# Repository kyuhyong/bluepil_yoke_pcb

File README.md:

# bluepil_yoke_pcb
# bluepil_yoke_pcb

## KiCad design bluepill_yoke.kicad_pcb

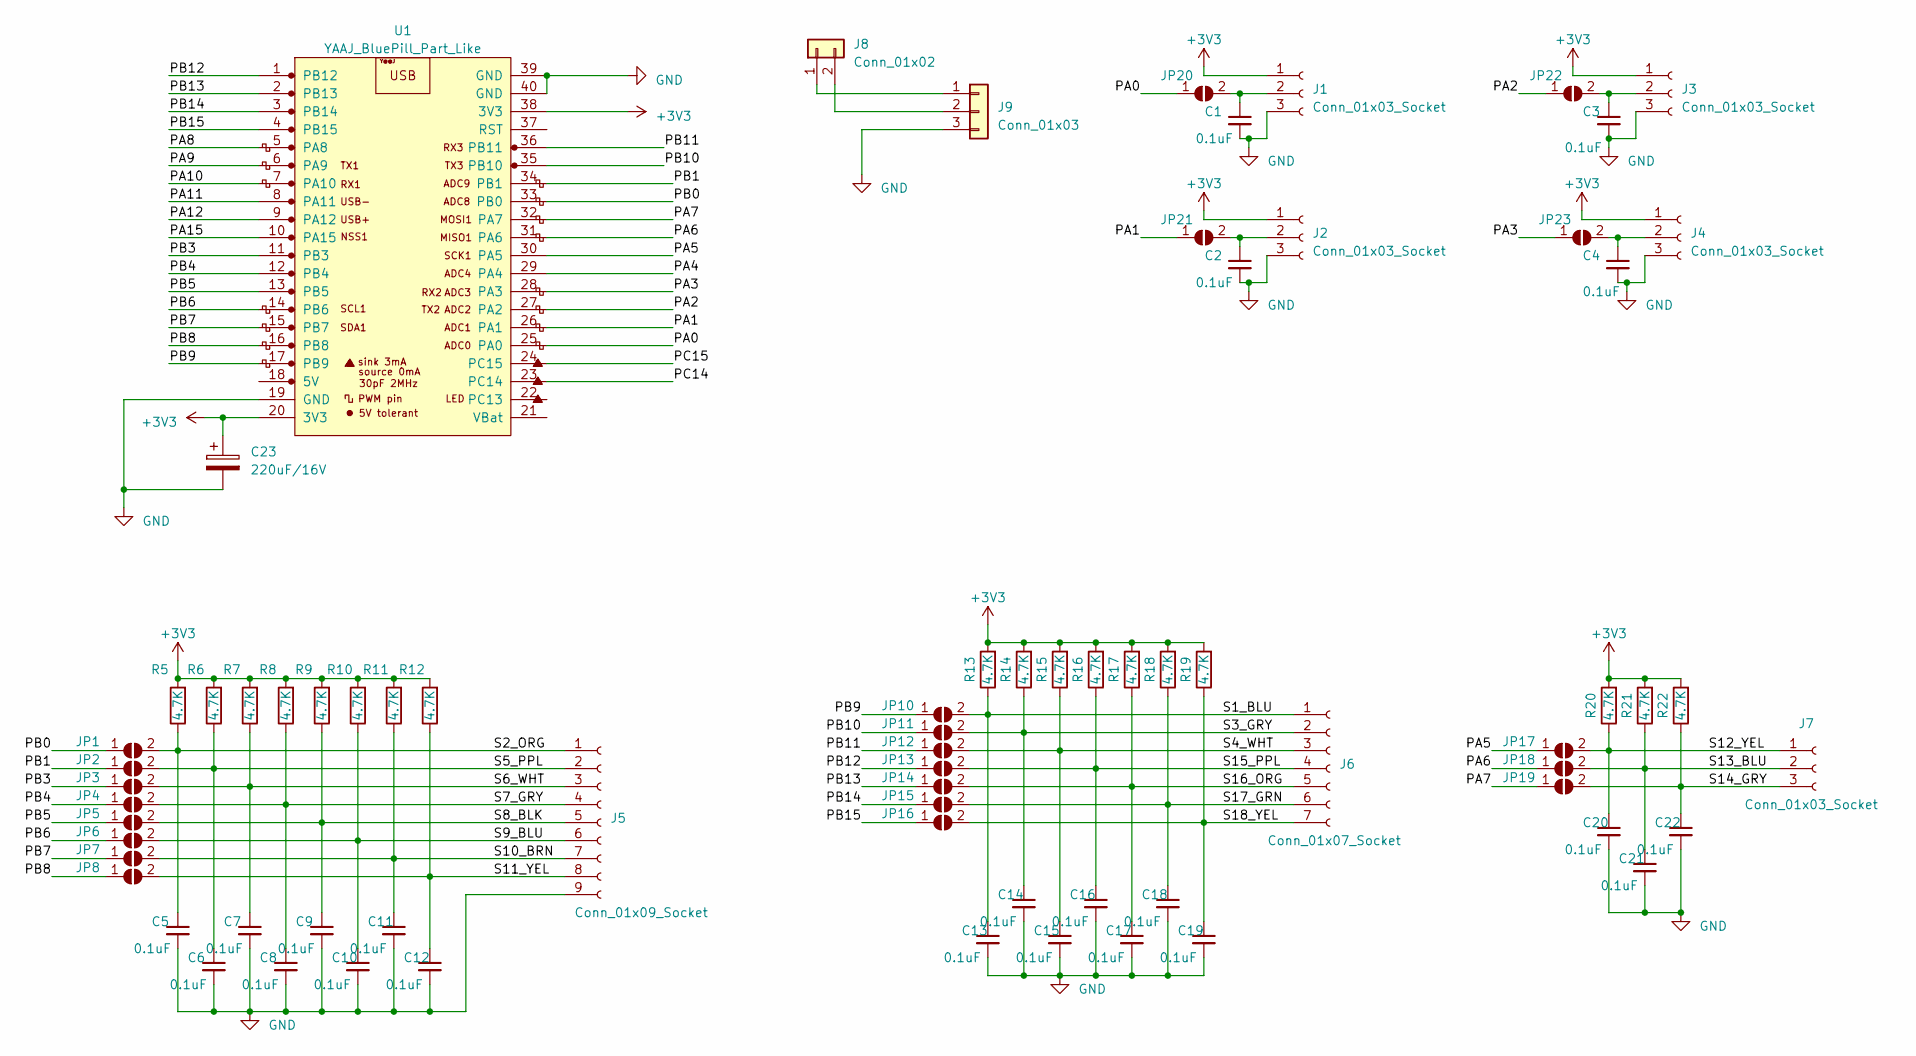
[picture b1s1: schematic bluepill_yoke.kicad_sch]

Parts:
C1, C2, C3, C4, C5, C6, C7, C8, C9, C10, C11, C12, C13, C14, C15, C16, C17, C18, C19, C20, C21, C22: 0.1uF; C_0603_1608Metric; MPN CC0603KRX7R9BB104; JLCPN C14663
C23: 220uF/16V; CP_Radial_D6.3mm_P2.50mm; MPN MHA 16V220 6.3*11; JLCPN C165514
J1, J2, J3, J4: Conn_01x03_Socket; PinHeader_1x03_P2.54mm_Vertical
J5: Conn_01x09_Socket; PinHeader_1x09_P2.00mm_Vertical
J6: Conn_01x07_Socket; PinSocket_1x07_P2.00mm_Vertical
J7: Conn_01x03_Socket; PinHeader_1x03_P2.00mm_Vertical
J8: Conn_01x02; PinHeader_1x02_P2.54mm_Vertical
J9: Conn_01x03; PinHeader_1x03_P2.54mm_Horizontal
JP1, JP2, JP3, JP4, JP5, JP6, JP7, JP8, JP10, JP11, JP12, JP13, JP14, JP15, JP16, JP17, JP18, JP19, JP20, JP21, JP22, JP23: SolderJumper_2_Open; SolderJumper-2_P1.3mm_Open_TrianglePad1.0x1.5mm
R5, R6, R7, R8, R9, R10, R11, R12, R13, R14, R15, R16, R17, R18, R19, R20, R21, R22: 4.7K; R_0603_1608Metric; MPN RC0603JR-074K7L; JLCPN C105428
U1: YAAJ_BluePill_Part_Like; YAAJ_BluePill_Default

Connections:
+3V3: C23.1, J1.1, J2.1, J3.1, J4.1, R5.2, R6.2, R7.2, R8.2, R9.2, R10.2, R11.2, R12.2, R13.2, R14.2, R15.2, R16.2, R17.2, R18.2, R19.2, R20.2, R21.2, R22.2, U1.20 (3V3), U1.38 (3V3)
/PA0: JP20.1 (A), U1.25 (PA0)
/PA1: JP21.1 (A), U1.26 (PA1)
/PA2: JP22.1 (A), U1.27 (PA2)
/PA3: JP23.1 (A), U1.28 (PA3)
/PA4: U1.29 (PA4)
/PA5: JP17.1 (A), U1.30 (PA5)
/PA6: JP18.1 (A), U1.31 (PA6)
/PA7: JP19.1 (A), U1.32 (PA7)
/PA8: U1.5 (PA8)
/PA9: U1.6 (PA9)
/PA10: U1.7 (PA10)
/PA11: U1.8 (PA11)
/PA12: U1.9 (PA12)
/PA15: U1.10 (PA15)
/PB0: JP1.1 (A), U1.33 (PB0)
/PB1: JP2.1 (A), U1.34 (PB1)
/PB3: JP3.1 (A), U1.11 (PB3)
/PB4: JP4.1 (A), U1.12 (PB4)
/PB5: JP5.1 (A), U1.13 (PB5)
/PB6: JP6.1 (A), U1.14 (PB6)
/PB7: JP7.1 (A), U1.15 (PB7)
/PB8: JP8.1 (A), U1.16 (PB8)
/PB9: JP10.1 (A), U1.17 (PB9)
/PB10: JP11.1 (A), U1.35 (PB10)
/PB11: JP12.1 (A), U1.36 (PB11)
/PB12: JP13.1 (A), U1.1 (PB12)
/PB13: JP14.1 (A), U1.2 (PB13)
/PB14: JP15.1 (A), U1.3 (PB14)
/PB15: JP16.1 (A), U1.4 (PB15)
/PC14: U1.23 (PC14)
/PC15: U1.24 (PC15)
/S1_BLU: C13.1, J6.1, JP10.2 (B), R13.1
/S2_ORG: C5.1, J5.1, JP1.2 (B), R5.1
/S3_GRY: C14.1, J6.2, JP11.2 (B), R14.1
/S4_WHT: C15.1, J6.3, JP12.2 (B), R15.1
/S5_PPL: C6.1, J5.2, JP2.2 (B), R6.1
/S6_WHT: C7.1, J5.3, JP3.2 (B), R7.1
/S7_GRY: C8.1, J5.4, JP4.2 (B), R8.1
/S8_BLK: C9.1, J5.5, JP5.2 (B), R9.1
/S9_BLU: C10.1, J5.6, JP6.2 (B), R10.1
/S10_BRN: C11.1, J5.7, JP7.2 (B), R11.1
/S11_YEL: C12.1, J5.8, JP8.2 (B), R12.1
/S12_YEL: C20.1, J7.1, JP17.2 (B), R20.1
/S13_BLU: C21.1, J7.2, JP18.2 (B), R21.1
/S14_GRY: C22.1, J7.3, JP19.2 (B), R22.1
/S15_PPL: C16.1, J6.4, JP13.2 (B), R16.1
/S16_ORG: C17.1, J6.5, JP14.2 (B), R17.1
/S17_GRN: C18.1, J6.6, JP15.2 (B), R18.1
/S18_YEL: C19.1, J6.7, JP16.2 (B), R19.1
GND: C1.2, C2.2, C3.2, C4.2, C5.2, C6.2, C7.2, C8.2, C9.2, C10.2, C11.2, C12.2, C13.2, C14.2, C15.2, C16.2, C17.2, C18.2, C19.2, C20.2, C21.2, C22.2, C23.2, J1.3, J2.3, J3.3, J4.3, J5.9, J9.3, U1.19 (GND), U1.39 (GND), U1.40 (GND)
unnamed: C1.1, J1.2, JP20.2 (B)
unnamed: C2.1, J2.2, JP21.2 (B)
unnamed: C3.1, J3.2, JP22.2 (B)
unnamed: C4.1, J4.2, JP23.2 (B)
unnamed: J8.1, J9.1
unnamed: J8.2, J9.2

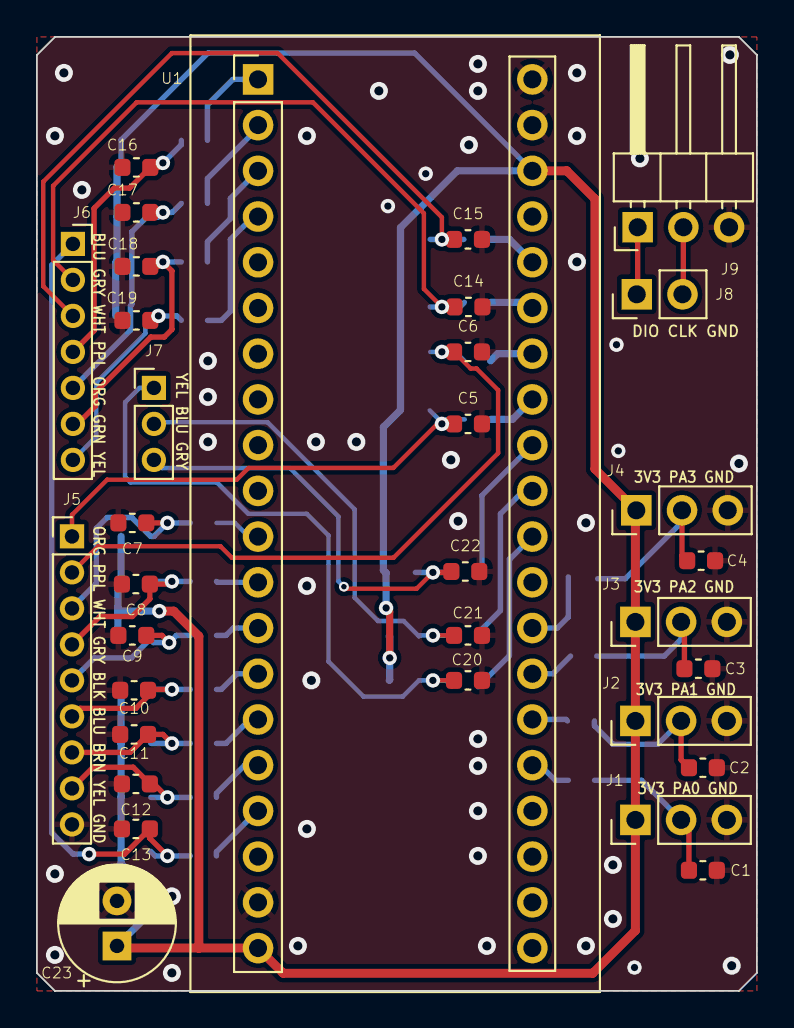
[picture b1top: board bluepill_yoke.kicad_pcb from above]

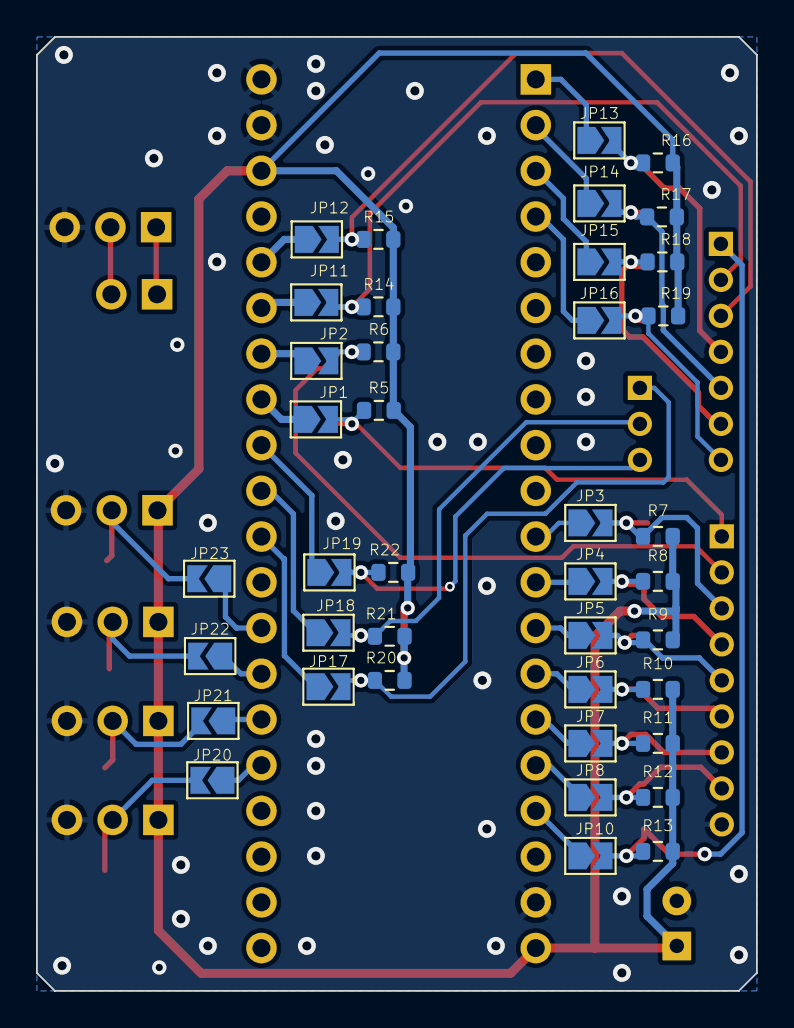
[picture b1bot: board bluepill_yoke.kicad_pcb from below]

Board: 2 copper layers, 40.0 x 53.0 mm, 73 parts (40 on the bottom side), 48 nets.

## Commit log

2023-07-25 Finished pcb
2023-08-05 Updated docs
